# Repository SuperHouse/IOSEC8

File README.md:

Security Sensor Breakout
========================
Copyright 2017-2019 SuperHouse Automation Pty Ltd: www.superhouse.tv  

Based on the circuit described in the "Security / Automation Sensors"
project in the book "Practical Arduino", this breakout allows up to 8
security sensors to be connected with full End-Of-Line (EOL) support to
detect tampering.

Supported sensors include:

 * PIR (passive infrared) motion detectors.
 * Microwave motion detectors.
 * Reed switches.
 * Glass break detectors.
 * Gas detectors.

End-Of-Line technology allows the system to detect a variety of events
using a single cable pair to the sensor, including:

 * Sensor triggered.
 * Sensor cable cut.
 * Sensor cable short-circuited.
 * Sensor housing opened (even when system is disarmed)

Compatible with I/O breakouts such as the I/O Breakout and I/O Breakout
Mega, both from SuperHouse.

Features:

 * Supports 8 sensor channels simultaneously.
 * Sensor power supply connections.
 * "Sensor power on" LED.
 * Optional status LEDs for each channel

More information is available at:

  http://www.superhouse.tv/iosec8  

INSTALLATION
------------
The design is saved as an EAGLE project. EAGLE PCB design software is
available from www.cadsoftusa.com free for non-commercial use. To use
this project download it and place the directory containing these files
into the "eagle" directory on your computer. Then open EAGLE and
navigate to the project.

DISTRIBUTION
------------
The specific terms of distribution of this project are governed by the
license referenced below.

LICENSE
-------
Licensed under the TAPR Open Hardware License (www.tapr.org/OHL).
The "license" folder within this repository also contains a copy of
this license in plain text format.

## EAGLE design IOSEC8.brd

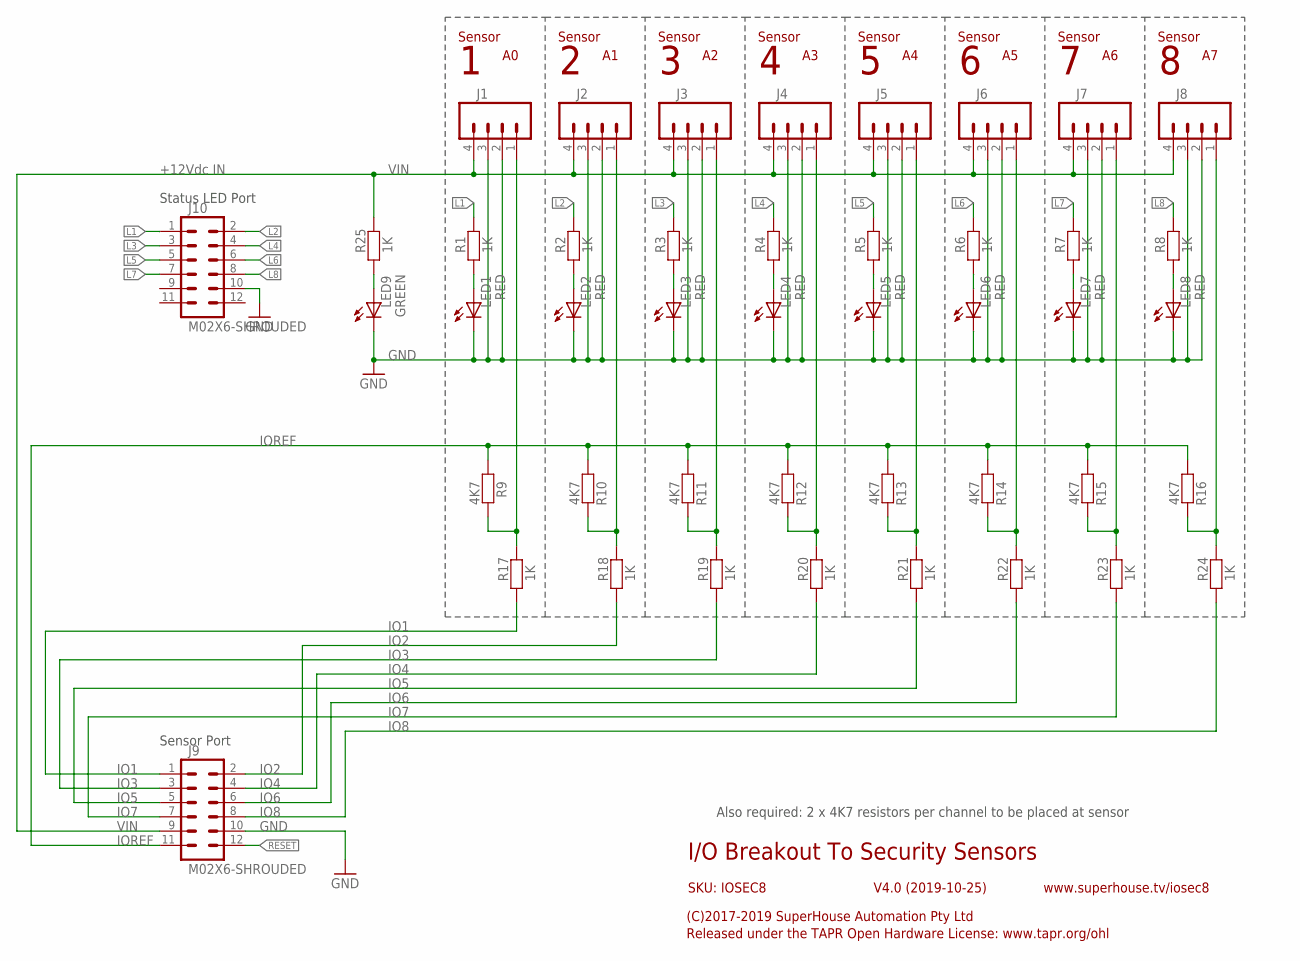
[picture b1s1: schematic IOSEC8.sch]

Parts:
J1, J2, J3, J4, J5, J6, J7, J8: M04-SCREW-3.5MM; SCREWTERMINAL-3.5MM-4
J9, J10: M02X6-SHROUDED; 2X06-SHROUDED
LED1, LED2, LED3, LED4, LED5, LED6, LED7, LED8: RED; LED-0603
LED9: GREEN; LED-0603
R1, R2, R3, R4, R5, R6, R7, R8, R17, R18, R19, R20, R21, R22, R23, R24, R25: 1K; R0603
R9, R10, R11, R12, R13, R14, R15, R16: 4K7; R0603

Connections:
GND: J1.2, J1.3, J2.2, J2.3, J3.2, J3.3, J4.2, J4.3, J5.2, J5.3, J6.2, J6.3, J7.2, J7.3, J8.2, J8.3, J9.10, J10.10, LED1.C, LED2.C, LED3.C, LED4.C, LED5.C, LED6.C, LED7.C, LED8.C, LED9.C
IO1: J9.1, R17.1
IO2: J9.2, R18.1
IO3: J9.3, R19.1
IO4: J9.4, R20.1
IO5: J9.5, R21.1
IO6: J9.6, R22.1
IO7: J9.7, R23.1
IO8: J9.8, R24.1
IOREF: J9.11, R9.1, R10.1, R11.1, R12.1, R13.1, R14.1, R15.1, R16.1
L1: J10.1, R1.2
L2: J10.2, R2.2
L3: J10.3, R3.2
L4: J10.4, R4.2
L5: J10.5, R5.2
L6: J10.6, R6.2
L7: J10.7, R7.2
L8: J10.8, R8.2
unnamed: LED9.A, R25.1
unnamed: LED1.A, R1.1
unnamed: J2.1, R10.2, R18.2
unnamed: J5.1, R13.2, R21.2
unnamed: J6.1, R14.2, R22.2
unnamed: J7.1, R15.2, R23.2
unnamed: J8.1, R16.2, R24.2
unnamed: LED2.A, R2.1
unnamed: LED3.A, R3.1
unnamed: LED4.A, R4.1
unnamed: LED5.A, R5.1
unnamed: LED6.A, R6.1
unnamed: LED7.A, R7.1
unnamed: LED8.A, R8.1
unnamed: J3.1, R11.2, R19.2
unnamed: J4.1, R12.2, R20.2
unnamed: J1.1, R9.2, R17.2
RESET: J9.12
VIN: J1.4, J2.4, J3.4, J4.4, J5.4, J6.4, J7.4, J8.4, J9.9, R25.2

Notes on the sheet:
Sensor
+12Vdc IN
I/O Breakout To Security Sensors
V4.0 (2019-10-25)
SKU: IOSEC8
(C)2017-2019 SuperHouse Automation Pty Ltd
Released under the TAPR Open Hardware License: www.tapr.org/ohl
www.superhouse.tv/iosec8
Also required: 2 x 4K7 resistors per channel to be placed at sensor
Sensor Port
Status LED Port

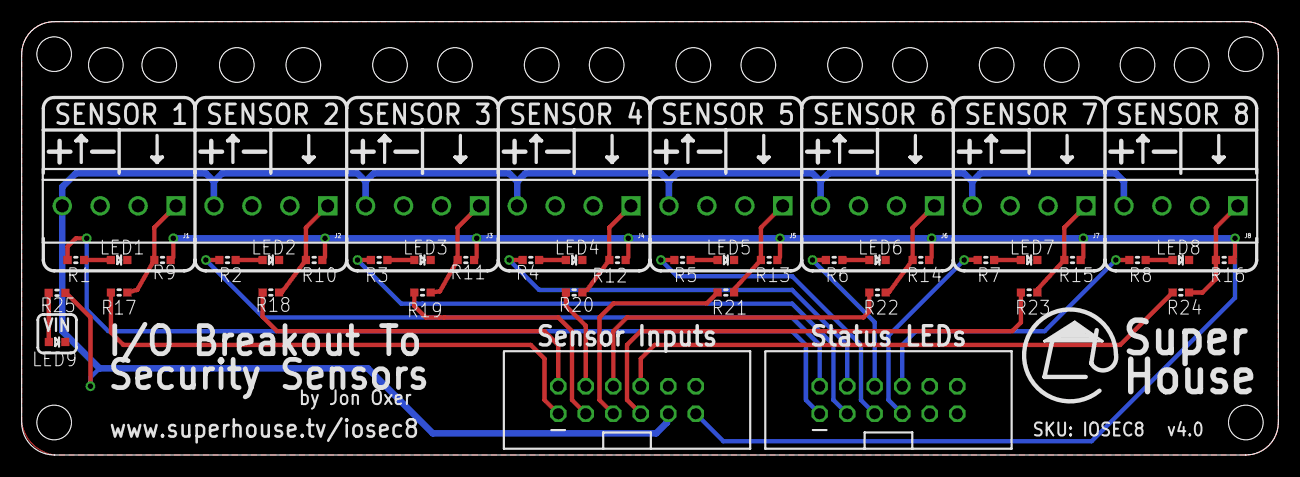
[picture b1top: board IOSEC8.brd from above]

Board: 2 copper layers, 116.0 x 40.0 mm, 44 parts (0 on the bottom side), 36 nets.

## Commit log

2017-07-25 Initial project import
2017-07-25 Moved to metric grid for v2.0 release
2017-08-03 Improved position of part designators
2018-01-24 Added second IO port for status LEDs. Ready for v3.0 release
2018-04-11 Improved value labels for assembly guide
2019-10-25 Massive update to reduce PCB size for v4.0 release
2019-10-25 Added render
